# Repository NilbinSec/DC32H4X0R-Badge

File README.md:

# USING THE MOMENTARY SWITCHES MAY DAMAGE YOUR DEFCON BADGE IN AN UNRECOVERABLE WAY YOU HAVE BEEN WARNED! See Below...

## DC32H4X0R-Badge

Did you see the latest announcement from Defcon about the badge this year? So did we! We love CTFs and suspect that the two GPIO pins on the badge this year might be used during the badge challenge this year so NilbinSec is publishing a really shitty SAO (like our shard last year) to enable interaction with the GPIO pins for anyone who might need it.

The gerber file has already been shared on OSHPark, and is probably the cheapest, quickest way to get yourself one of these badges before Defcon this year if you plan on working on the badge challenge.

https://oshpark.com/shared_projects/B9nO6Rdw

# USE AT YOUR OWN RISK
We can't stress this enough, we only have a single image provided by the Defcon organizers https://x.com/defcon/status/1808279118477418640

We are uncertain what the intent of these GPIO pins are for and what if any functionality they might have in the base badge. But with the risks, we wanted to make sure people that might need something like this have it available to interact with their badges. Just recognize that there is a risk anytime you start hacking on something.

# USING THE MOMENTARY SWITCHES MAY DAMAGE YOUR DEFCON BADGE IN AN UNRECOVERABLE WAY YOU HAVE BEEN WARNED!

## BOM

1x DC32H4X0R PCB

2x 6mmx6mm momentary switch 
https://www.aliexpress.us/item/2251832725948381.html

1x 2x3 shrouded SAO header 
https://www.aliexpress.us/item/2251801533330071.html

**The below is not strictly required for the GPIO interaction, just gives a minimum of blinky**

1x 0805 470 Ohm Resistor

2x 0805/0807 RGB Slow Flash LEDs
https://www.aliexpress.us/w/wholesale-0807-rgb-led-slow-flashing.html
 
  Any 0805 RGB LED will work

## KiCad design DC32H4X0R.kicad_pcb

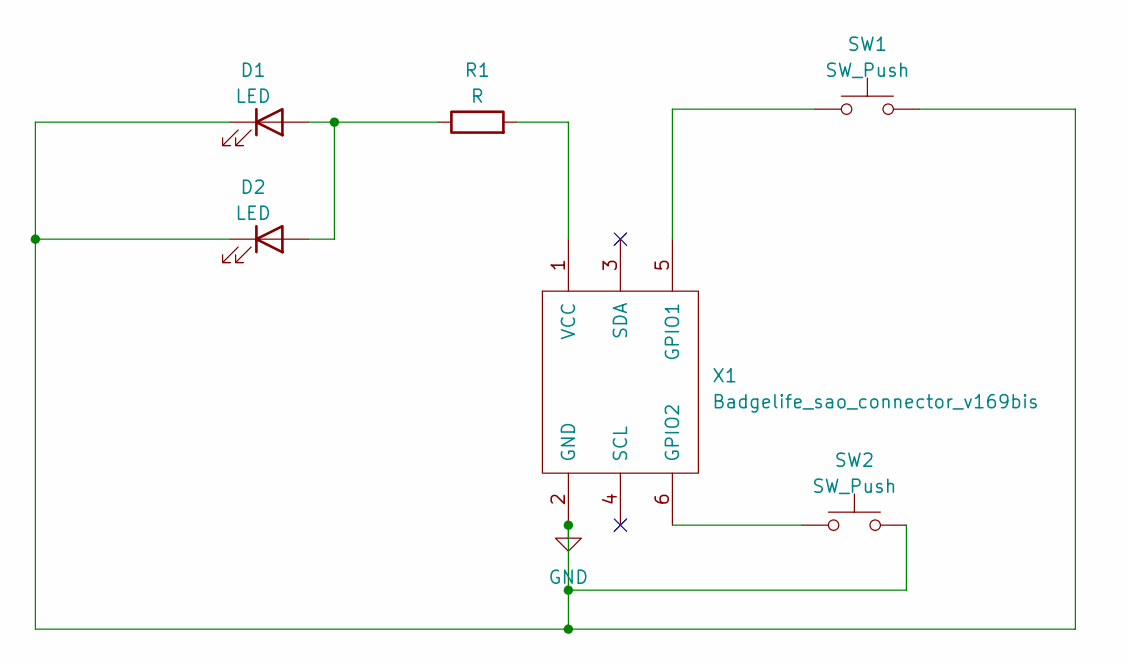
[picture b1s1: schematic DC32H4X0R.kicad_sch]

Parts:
D1: LED; LED_0603_1608Metric_Pad1.05x0.95mm_HandSolder
D2: LED; LED_0805_2012Metric_Pad1.15x1.40mm_HandSolder
R1: R; R_0805_2012Metric_Pad1.20x1.40mm_HandSolder
SW1, SW2: SW_Push; SW_PUSH_6mm
X1: Badgelife_sao_connector_v169bis; Badgelife-SAOv169-SAO-2x3

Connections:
GND: D1.1 (K), D2.1 (K), SW1.2, SW2.2, X1.2 (GND)
unnamed: D1.2 (A), D2.2 (A), R1.1
unnamed: SW1.1, X1.5 (GPIO1)
unnamed: SW2.1, X1.6 (GPIO2)
unnamed: R1.2, X1.1 (VCC)

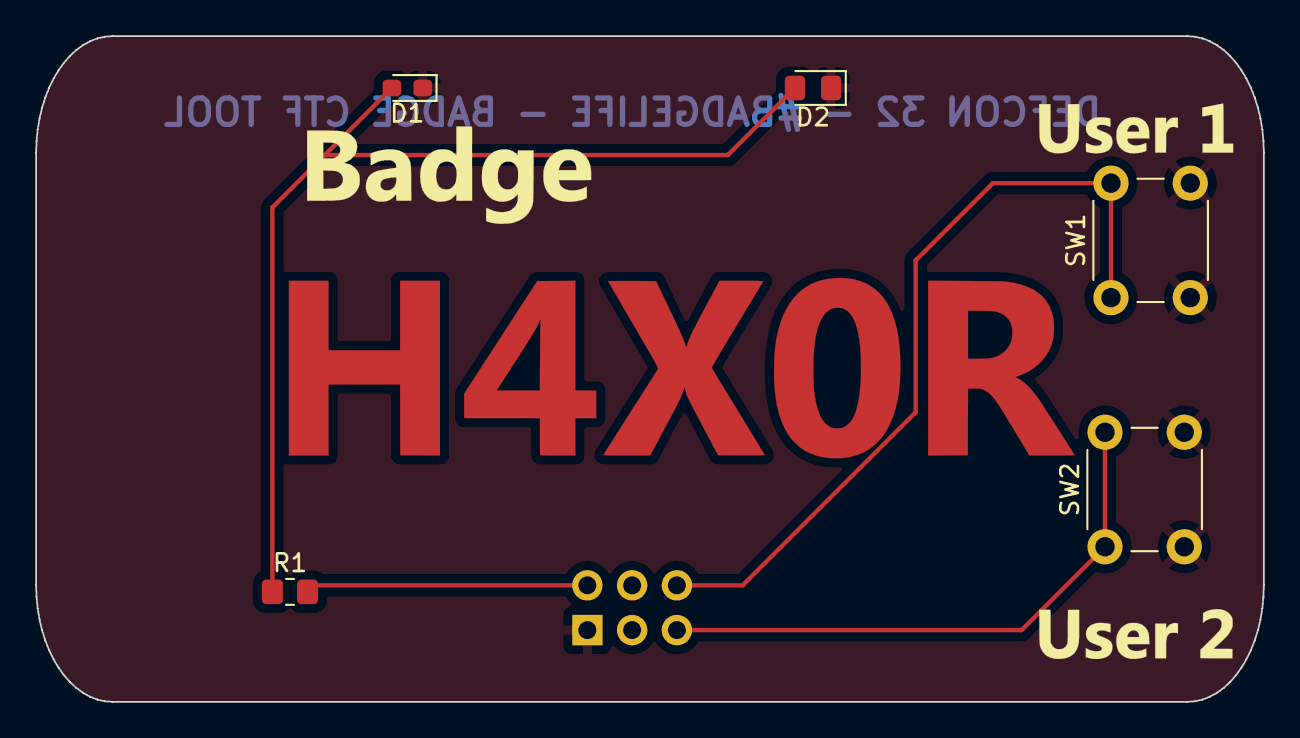
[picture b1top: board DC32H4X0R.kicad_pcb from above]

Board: 2 copper layers, 69.7 x 37.8 mm, 6 parts (0 on the bottom side), 5 nets.

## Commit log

2024-07-03 Update README.md
    Added OshPark Link
2024-07-03 Update README.md
    typo
